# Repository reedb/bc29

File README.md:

Generate a schematic for the Brusa BC29 Ampere hour meter in CADSOFT Eagle format.

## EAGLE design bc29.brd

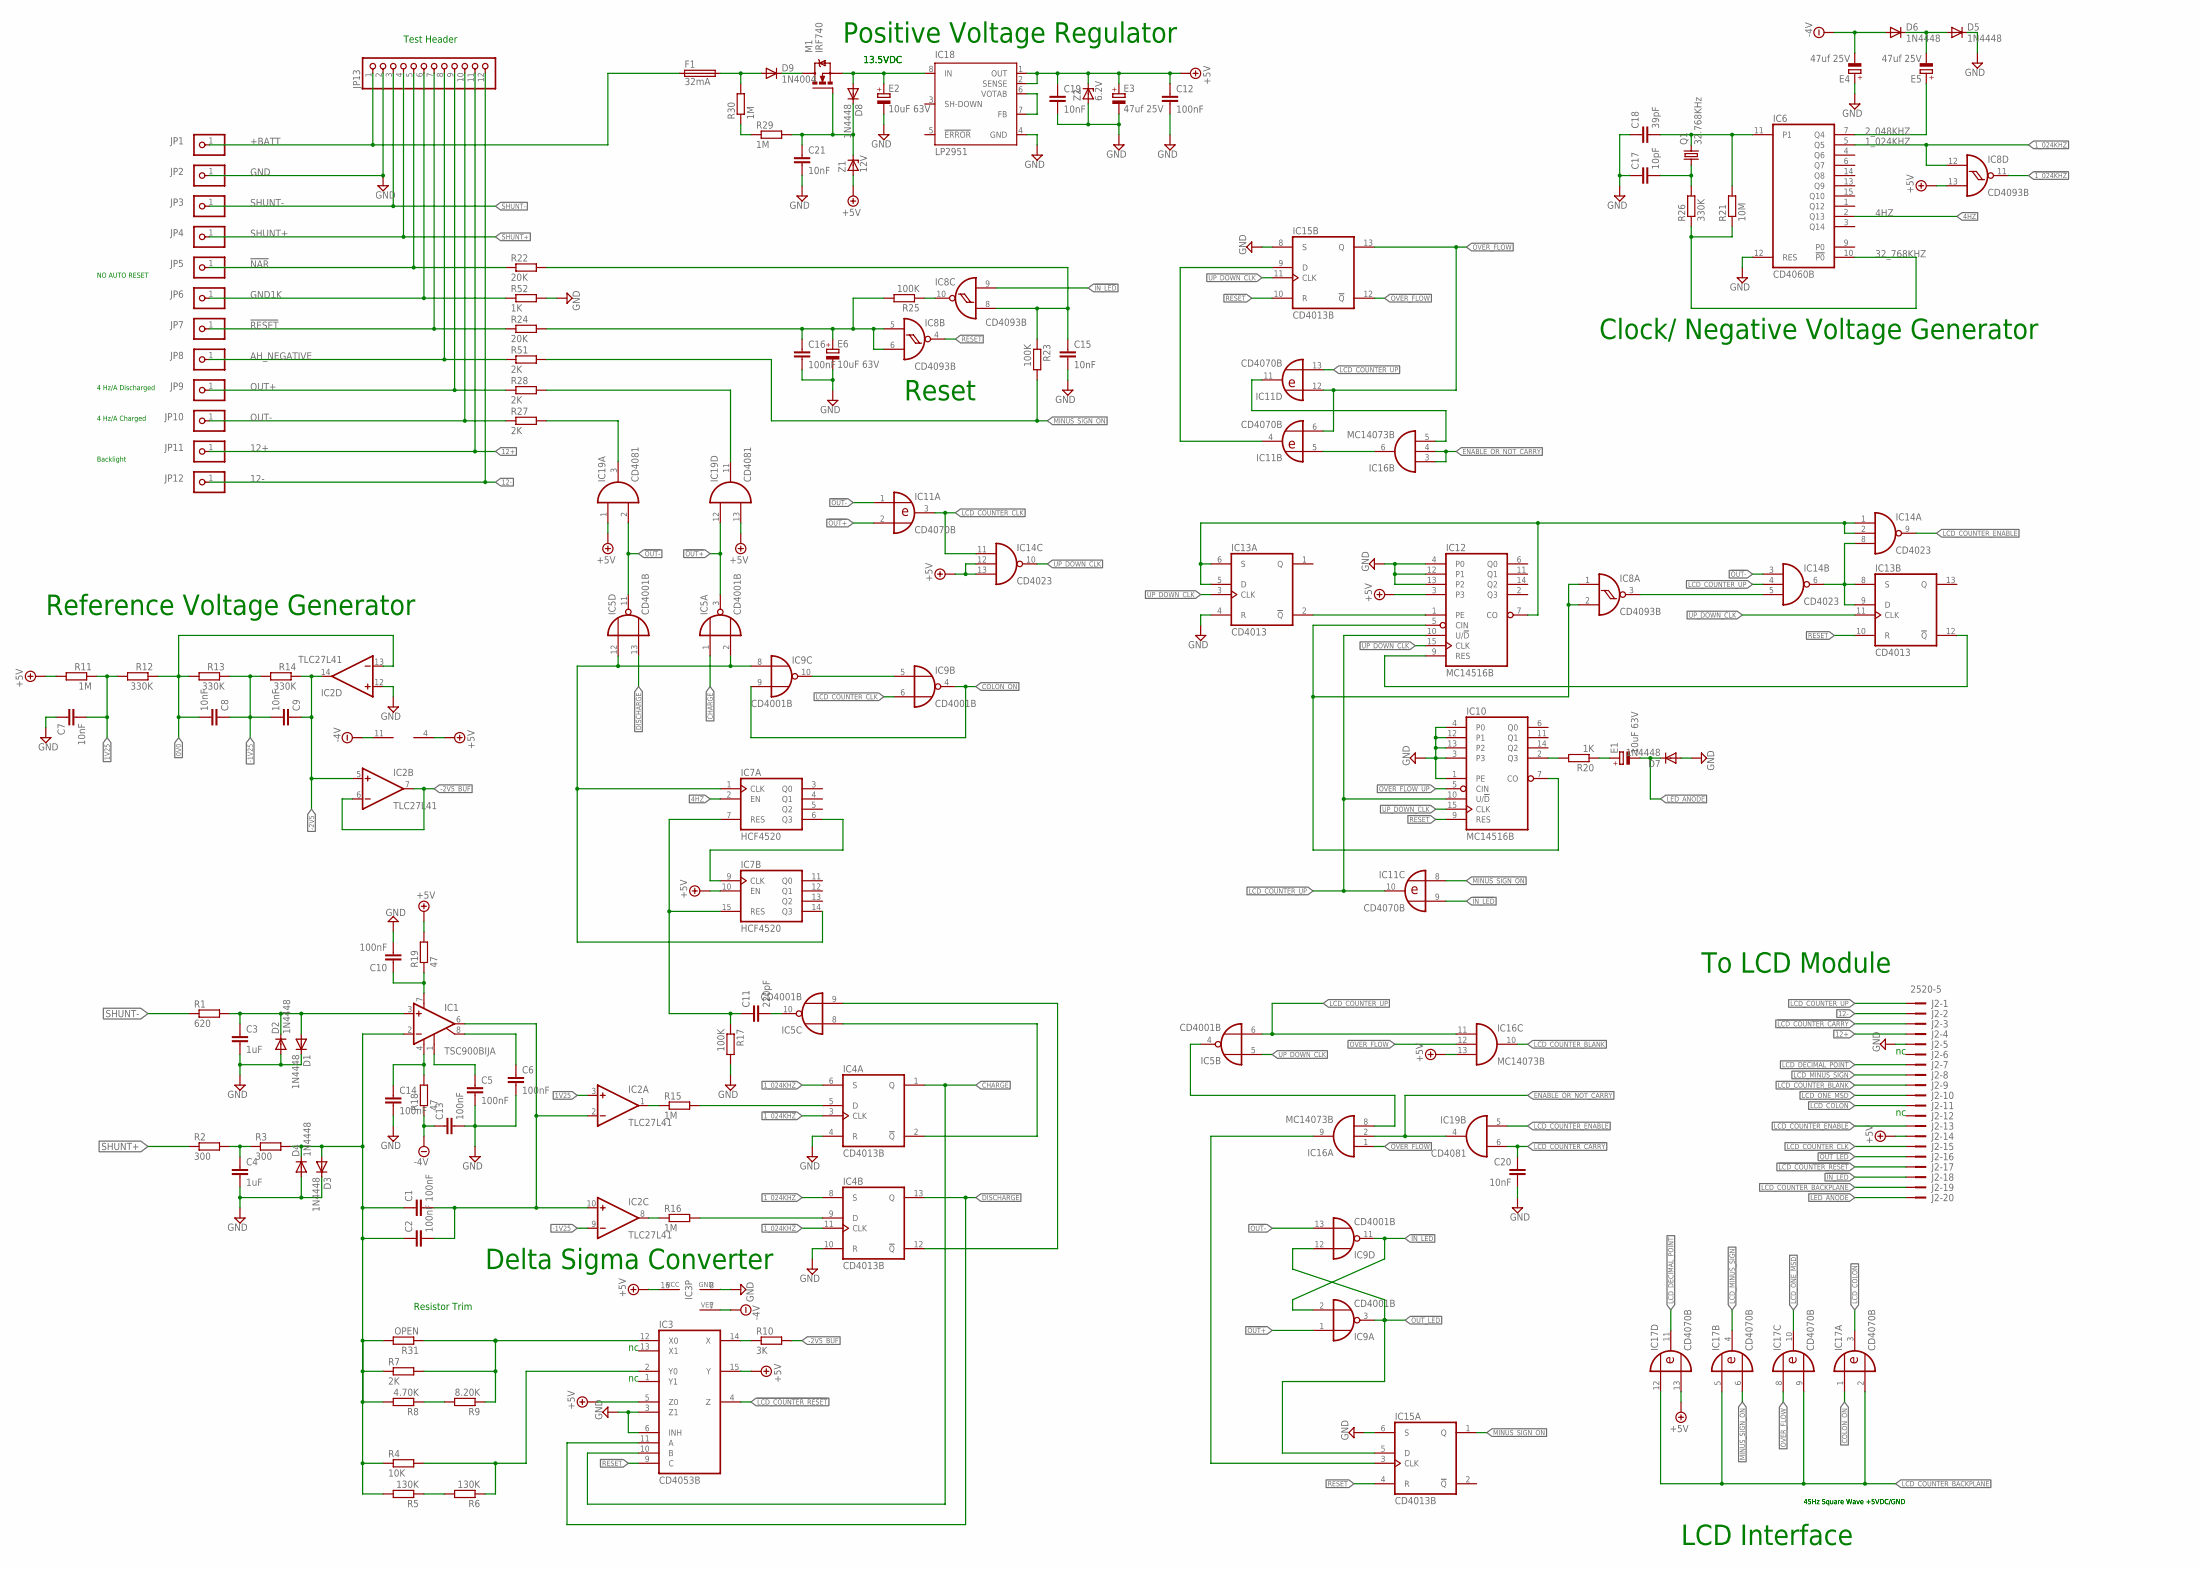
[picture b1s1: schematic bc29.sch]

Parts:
C1, C2, C5, C6, C10, C12, C13, C14, C16: 100nF; C1206
C3, C4: 1uF; C050-045X075
C7, C8, C9, C15, C19, C21: 10nF; C0805
C11: 220pF; C0805
C17: 10pF; C0805
C18: 39pF; C0805
C20: 10nF; C050-024X044
D1, D2, D3, D4, D5, D6, D7, D8: 1N4448; MINIMELF
D9: 1N4004; SOD80C
E1, E2, E6: 10uF 63V; E2,5-5
E3, E4, E5: 47uf 25V; E2,5-5
F1: 32mA; FUSE_HOLDER_5X20MM
IC1: TSC900BIJA; DIL08
IC2: TLC27L41; SO14
IC3: CD4053B; SO16
IC4, IC15: CD4013B; SO14
IC5, IC9: CD4001B; SO14
IC6: CD4060B; SO16
IC7: HCF4520; SO16
IC8: CD4093B; SO14
IC10, IC12: MC14516B; SO16
IC11, IC17: CD4070B; SO14
IC13: CD4013; SO14
IC14: CD4023; SO14
IC16: MC14073B; SO14
IC18: LP2951; SO08
IC19: CD4081; SO14
J2: 2520-5; PAK100/2500-5-20
JP1, JP2, JP3, JP4, JP5, JP6, JP7, JP8, JP9, JP10, JP11, JP12: PINHD-1X1; 1X01
JP13: PINHD-1X12; 1X12
M1: IRF740; TO220BV
Q1: 32.768KHz; TC26H
R1: 620; M0805
R2, R3: 300; M0805
R4: 10K; M0805
R5, R6: 130K; 0207/10
R7, R27, R28, R51: 2K; M0805
R8: 4.70K; 0207/10
R9: 8.20K; 0207/10
R10: 3K; M0805
R11, R15, R16, R29, R30: 1M; M0805
R12, R13, R14, R26: 330K; M0805
R17, R23, R25: 100K; M0805
R18, R19: 47; M0805
R20, R52: 1K; M0805
R21: 10M; M0805
R22, R24: 20K; M0805
R31: OPEN; 0207/10
Z1: 12V; SOD80C
Z2: 6.2V; SOD80C

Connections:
0V0: C8.2, IC2.13 (-IN), R12.1, R13.2
1V25: C7.2, IC2.3 (+IN), R11.1, R12.2
1_024KHZ: IC4.6 (S), IC4.8 (S), IC6.5 (Q5), IC8.12 (I0)
2_048KHZ: E5.+, IC6.7 (Q4)
4HZ: IC6.2 (Q13), IC7.2 (EN)
12+: J2.4, JP11.1, JP13.11
12-: J2.2, JP12.1, JP13.12
13V5: D8.A, E2.+, IC18.8 (IN), M1.S
32_768KHZ: IC6.10 (!P0), R21.1, R26.1
!1_024KHZ: IC4.3 (CLK), IC4.11 (CLK), IC8.11 (O)
!CHARGE: IC4.2 (!Q), IC5.8 (I0)
!DISCHARGE: IC4.12 (!Q), IC5.9 (I1)
!IN_LED: IC8.9 (I1), IC9.2 (I1), IC9.11 (O), IC11.9 (I1), J2.18
!LCD_COUNTER_CARRY: C20.1, IC19.6 (I1), J2.3
!LCD_COUNTER_RESET: IC3.4 (Z), J2.17
!NAR: JP5.1, JP13.5, R22.1
!NAR_R: C15.1, IC8.8 (I0), R22.2, R23.1
!OUT+: IC5.3 (O), IC9.1 (I0), IC11.2 (I1), IC19.12 (I0)
!OUT-: IC5.11 (O), IC9.13 (I1), IC11.1 (I0), IC14.3 (I0), IC19.2 (I1)
!OUT_LED: IC9.3 (O), IC9.12 (I0), IC15.5 (D), J2.16
!OVER_FLOW: IC15.12 (!Q), IC16.1 (I0)
!RESET: JP7.1, JP13.7, R24.1
+5V: C12.1, C19.1, E3.+, IC2.4 (V+), IC3.5 (Z0), IC3.15 (Y), IC3.16 (VCC), IC7.10 (EN), IC8.13 (I1), IC12.3, IC14.12 (I1), IC14.13 (I2), IC16.13 (I2), IC17.13 (I1), IC18.1 (OUT), IC18.2 (SENSE), IC19.1 (I0), IC19.13 (I1), J2.14, R11.2, R19.2, Z1.A, Z2.C
+BATT: F1.1, JP1.1, JP13.1
-1V25: C8.1, C9.2, IC2.9 (-IN), R13.1, R14.2
-2V5: C9.1, IC2.5 (+IN), IC2.14 (OUT), R14.1
-2V5_BUF: IC2.6 (-IN), IC2.7 (OUT), R10.2
-2V5_BUF_R: IC3.14 (X), R10.1
-4V: D6.A, E4.-
-5V: C13.1, IC2.11 (V-), IC3.7 (VEE), R18.1
AH_NEGATIVE: JP8.1, JP13.8, R51.1
CHARGE: IC3.10 (B), IC4.1 (Q), IC5.1 (I0)
COLON_ON: IC9.4 (O), IC9.9 (I1), IC17.1 (I0)
CXA: C5.1, IC1.1 (CMP1)
CXB: C6.1, IC1.8 (CMP2)
DISCHARGE: IC3.11 (A), IC4.13 (Q), IC5.13 (I1)
DRAIN: D9.C, M1.D
D_CHARGE: IC4.5 (D), R15.2
D_DISCHARGE: IC4.9 (D), R16.2
ENABLE_OR_NOT_CARRY: IC16.2 (I1), IC16.3 (I0), IC16.4 (I1), IC19.4 (O)
FUSED_BATT+: D9.A, F1.2, R30.2
GATE: C21.1, D8.C, M1.G, R29.2, Z1.C
GND: C3.2, C4.2, C5.2, C6.2, C7.1, C10.2, C12.2, C13.2, C14.2, C15.2, C16.2, C17.1, C18.1, C19.2, C20.2, C21.2, D1.C, D2.A, D3.C, D4.A, D5.C, D7.A, E2.-, E3.-, E4.+, E6.-, IC2.12 (+IN), IC3.3 (Z1), IC3.6 (INH), IC3.8 (GND), IC4.4 (R), IC4.10 (R), IC6.12 (RES), IC10.1 (PE), IC10.3, IC10.4 (P0), IC10.12 (P1), IC10.13 (P2), IC12.4 (P0), IC12.12 (P1), IC12.13 (P2), IC13.4 (R), IC15.6 (S), IC15.8 (S), IC18.4 (GND), J2.5, JP2.1, JP13.2, R17.2, R52.2, Z2.A
GND1K: JP6.1, JP13.6, R52.1
IC3-11: IC11.11 (O), IC16.5 (I2)
IC5-4: IC5.4 (O), IC16.8 (I2)
IC7-14: IC5.2 (I1), IC5.12 (I0), IC7.1 (CLK), IC7.14 (Q3), IC9.8 (I0)
IC8-3: IC8.3 (O), IC14.5 (I2)
IC10-7: IC8.1 (I0), IC8.2 (I1), IC10.7 (CO), IC12.5 (CIN)
IC13-5: IC12.7 (CO), IC13.5 (D), IC13.6 (S), IC14.1 (I0), IC14.2 (I1)
IC14-6: IC13.8 (S), IC13.9 (D), IC14.6 (O), IC14.8 (I2)
IC15-3: IC15.3 (CLK), IC16.9 (O)
IN+: C3.1, D1.A, D2.C, IC1.3 (+IN), R1.2
IN-: C1.1, C2.1, D3.A, D4.C, IC1.2 (-IN), R3.2, R4.1, R5.2, R7.1, R8.2, R31.2
LCD_COLON: IC17.3 (O), J2.11
LCD_COUNTER_BACKPLANE: IC17.2 (I1), IC17.5 (I0), IC17.9 (I1), IC17.12 (I0), J2.19
LCD_COUNTER_BLANK: IC16.10 (O), J2.9
LCD_COUNTER_CLK: IC9.6 (I1), IC11.3 (O), IC14.11 (I0), J2.15
LCD_COUNTER_ENABLE: IC14.9 (O), IC19.5 (I0), J2.13
LCD_COUNTER_UP: IC5.6 (I1), IC10.10 (U/!D), IC11.10 (O), IC11.13 (I1), IC12.10 (U/!D), IC14.4 (I1), IC16.11 (I0), J2.1
LCD_DECIMAL_POINT: IC17.11 (O), J2.7
LCD_MINUS_SIGN: IC17.4 (O), J2.8
LCD_ONE_MSD: IC17.10 (O), J2.10
LED_ANODE: D7.C, E1.-, J2.20
MINUS_SIGN_ON: IC11.8 (I0), IC15.1 (Q), IC17.6 (I1), R23.2, R51.2
unnamed: C11.2, IC5.10 (O)
unnamed: IC12.9 (RES), IC13.12 (!Q)
unnamed: IC11.4 (O), IC15.9 (D)
unnamed: IC12.1 (PE), IC13.2 (!Q)
unnamed: IC7.6 (Q3), IC7.9 (CLK)
unnamed: C11.1, IC7.7 (RES), IC7.15 (RES), R17.1
unnamed: IC9.5 (I0), IC9.10 (O)
unnamed: IC11.5 (I0), IC16.6 (O)
unnamed: R29.1, R30.1
unnamed: IC10.2 (Q3), R20.2
unnamed: D5.A, D6.C, E5.-
unnamed: C17.2, Q1.1, R26.2
unnamed: C18.2, IC6.11 (P1), Q1.2, R21.2
unnamed: R5.1, R6.2
unnamed: IC18.6 (VOTAB), IC18.7 (FB)
unnamed: R8.1, R9.2
unnamed: IC8.10 (O), R25.1
unnamed: E1.+, R20.1
NEG_COMPARATOR: IC2.8 (OUT), R16.1
OP_AMP__OUT: C1.2, C2.2, IC1.6 (OUT), IC2.2 (-IN), IC2.10 (+IN)
OUT+: JP9.1, JP13.9, R28.1
OUT+_R: IC19.11 (O), R28.2
OUT-: JP10.1, JP13.10, R27.1
OUT-_R: IC19.3 (O), R27.2
OVER_FLOW: IC11.6 (I1), IC11.12 (I0), IC15.13 (Q), IC16.12 (I1), IC17.8 (I0)
OVER_FLOW_UP: IC10.5 (CIN)
POS_COMPARATOR: IC2.1 (OUT), R15.1
RESET: IC3.9 (C), IC8.4 (O), IC10.9 (RES), IC13.10 (R), IC15.4 (R), IC15.10 (R)
RESET_R: C16.1, E6.+, IC8.5 (I0), IC8.6 (I1), R24.2, R25.2
SHUNT+: JP4.1, JP13.4, R2.1
SHUNT+FILTER: C4.1, R2.2, R3.1
SHUNT-: JP3.1, JP13.3, R1.1
UP_DOWN_CLK: IC5.5 (I0), IC10.15 (CLK), IC12.15 (CLK), IC13.3 (CLK), IC13.11 (CLK), IC14.10 (O), IC15.11 (CLK)
VDD: IC4.14 (VDD), IC5.14 (VDD), IC6.16 (VDD), IC7.16 (VDD), IC8.14 (VDD), IC9.14 (VDD), IC10.16 (VDD), IC11.14 (VDD), IC12.16 (VDD), IC13.14 (VDD), IC14.14 (VDD), IC15.14 (VDD), IC16.14 (VDD), IC17.14 (VDD), IC19.14 (VDD)
VDD+: C10.1, IC1.7 (V+), R19.1
VDD-: C14.1, IC1.4 (V-), R18.2
VSS: IC4.7 (VSS), IC5.7 (VSS), IC6.8 (VSS), IC7.8 (VSS), IC8.7 (VSS), IC9.7 (VSS), IC10.8 (VSS), IC11.7 (VSS), IC12.8 (VSS), IC13.7 (VSS), IC14.7 (VSS), IC15.7 (VSS), IC16.7 (VSS), IC17.7 (VSS), IC19.7 (VSS)
X0: IC3.12 (X0), R7.2, R9.1, R31.1
Y0: IC3.2 (Y0), R4.2, R6.1

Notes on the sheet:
Test Header
13.5VDC
Resistor Trim
Delta Sigma Converter
NO AUTO RESET
4 Hz/A Discharged
4 Hz/A Charged
Backlight
Reference Voltage Generator
LCD Interface
Clock/ Negative Voltage Generator
Positive Voltage Regulator
To LCD Module
45Hz Square Wave +5VDC/GND
Reset

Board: 2 copper layers, 107 parts (0 on the bottom side), 103 nets, no tracks yet.

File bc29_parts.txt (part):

Partlist

Exported from bc29.sch at 2014-12-11 8:26 AM

EAGLE Version 7.1.0 Copyright (c) 1988-2014 CadSoft

Assembly variant: 

Part     Value          Device            Package            Library          Sheet

C1       100nF          C-EUC1206         C1206              rcl              1
C2       100nF          C-EUC1206         C1206              rcl              1
C3       1uF            C-EU050-045X075   C050-045X075       rcl              1
C4       1uF            C-EU050-045X075   C050-045X075       rcl              1
C5       100nF          C-EUC1206         C1206              rcl              1
C6       100nF          C-EUC1206         C1206              rcl              1
C7       10nF           C-EUC0805         C0805              rcl              1
C8       10nF           C-EUC0805         C0805              rcl              1
C9       10nF           C-EUC0805         C0805              rcl              1
C10      100nF          C-EUC1206         C1206              rcl              1
C11      220pF          C-EUC0805         C0805              rcl              1
C12      100nF          C-EUC1206         C1206              rcl              1
C13      100nF          C-EUC1206         C1206              rcl              1
C14      100nF          C-EUC1206         C1206              rcl              1
C15      10nF           C-EUC0805         C0805              rcl              1
C16      100nF          C-EUC1206         C1206              rcl              1
C17      10pF           C-EUC0805         C0805              rcl              1
C18      39pF           C-EUC0805         C0805              rcl              1
C19      10nF           C-EUC0805         C0805              rcl              1
C20      10nF           C-EU050-024X044   C050-024X044       rcl              1
C21      10nF           C-EUC0805         C0805              rcl              1
D1       1N4448         DIODE-MINIMELF    MINIMELF           diode            1
D2       1N4448         DIODE-MINIMELF    MINIMELF           diode            1
D3       1N4448         DIODE-MINIMELF    MINIMELF           diode            1
D4       1N4448         DIODE-MINIMELF    MINIMELF           diode            1
D5       1N4448         DIODE-MINIMELF    MINIMELF           diode            1
D6       1N4448         DIODE-MINIMELF    MINIMELF           diode            1
D7       1N4448         DIODE-MINIMELF    MINIMELF           diode            1
D8       1N4448         DIODE-MINIMELF    MINIMELF           diode            1
D9       1N4004         DIODE-SOD80C      SOD80C             diode            1
E1       10uF 63V       CPOL-EUE2.5-5     E2,5-5             rcl              1
E2       10uF 63V       CPOL-EUE2.5-5     E2,5-5             rcl              1
E3       47uf 25V       CPOL-EUE2.5-5     E2,5-5             rcl              1
E4       47uf 25V       CPOL-EUE2.5-5     E2,5-5             rcl              1
E5       47uf 25V       CPOL-EUE2.5-5     E2,5-5             rcl              1
E6       10uF 63V       CPOL-EUE2.5-5     E2,5-5             rcl              1
F1       32mA           FUSEBLANK_5X20MM  FUSE_HOLDER_5X20MM fuse             1
IC1      TSC900BIJA     2CMPN             DIL08              linear           1
IC2      TLC27L41       TLC274D           SO14               linear           1
IC3      CD4053B        4053D             SO16               40xx             1
IC4      CD4013B        4013D             SO14               40xx             1
IC5      CD4001B        4001D             SO14               40xx             1
IC6      CD4060B        4060D             SO16               40xx             1
IC7      HCF4520        4520D             SO16               45xx             1
IC8      CD4093B        4093D             SO14               40xx             1
IC9      CD4001B        4001D             SO14               40xx             1
IC10     MC14516B       4516D             SO16               45xx             1
IC11     CD4070B        4070D             SO14               40xx             1
IC12     MC14516B       4516D             SO16               45xx             1
IC13     CD4013         4013D             SO14               40xx             1
IC14     CD4023         4023D             SO14               40xx             1
IC15     CD4013B        4013D             SO14               40xx             1
IC16     MC14073B       4073D             SO14               40xx             1
IC17     CD4070B        4070D             SO14               40xx             1
IC18     LP2951         LP2951D           SO08               linear           1
IC19     CD4081         4081D             SO14               40xx             1
J1       2520-5         2520-5            PAK100/2500-5-20   con-3m           1
JP1                     PINHD-1X1         1X01               pinhead          1
JP2                     PINHD-1X1         1X01               pinhead          1
JP3                     PINHD-1X1         1X01               pinhead          1
JP4                     PINHD-1X1         1X01               pinhead          1
JP5                     PINHD-1X1         1X01               pinhead          1
JP6                     PINHD-1X1         1X01               pinhead          1
JP7                     PINHD-1X1         1X01               pinhead          1
JP8                     PINHD-1X1         1X01               pinhead          1
JP9                     PINHD-1X1         1X01               pinhead          1
JP10                    PINHD-1X1         1X01               pinhead          1
JP11                    PINHD-1X1         1X01               pinhead          1
JP12                    PINHD-1X1         1X01               pinhead          1
JP13                    PINHD-1X12        1X12               pinhead          1
M1       IRF740         IRF740            TO220BV            transistor-power 1
Q1       32.768KHz      CRYSTALTC26H      TC26H              crystal          1
R1       620            R-EU_M0805        M0805              rcl              1
R2       300            R-EU_M0805        M0805              rcl              1
R3       300            R-EU_M0805        M0805              rcl              1
R4       10K            R-EU_M0805        M0805              rcl              1
R5       130K           R-EU_0207/10      0207/10            rcl              1
R6       130K           R-EU_0207/10      0207/10            rcl              1
R7       2K             R-EU_M0805        M0805              rcl              1
R8       4.70K          R-EU_0207/10      0207/10            rcl              1
R9       8.20K          R-EU_0207/10      0207/10            rcl              1
R10      3K             R-EU_M0805        M0805              rcl              1
R11      1M             R-EU_M0805        M0805              rcl              1
R12      330K           R-EU_M0805        M0805              rcl              1
R13      330K           R-EU_M0805        M0805              rcl              1
R14      330K           R-EU_M0805        M0805              rcl              1
R15      1M             R-EU_M0805        M0805              rcl              1
R16      1M             R-EU_M0805        M0805              rcl              1
R17      100K           R-EU_M0805        M0805              rcl              1
R18      47             R-EU_M0805        M0805              rcl              1
R19      47             R-EU_M0805        M0805              rcl              1
R20      1K             R-EU_M0805        M0805              rcl              1
R21      10M            R-EU_M0805        M0805              rcl              1
R22      20K            R-EU_M0805        M0805              rcl              1
R23      100K           R-EU_M0805        M0805              rcl              1
R24      20K            R-EU_M0805        M0805              rcl              1
R25      100K           R-EU_M0805        M0805              rcl              1
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
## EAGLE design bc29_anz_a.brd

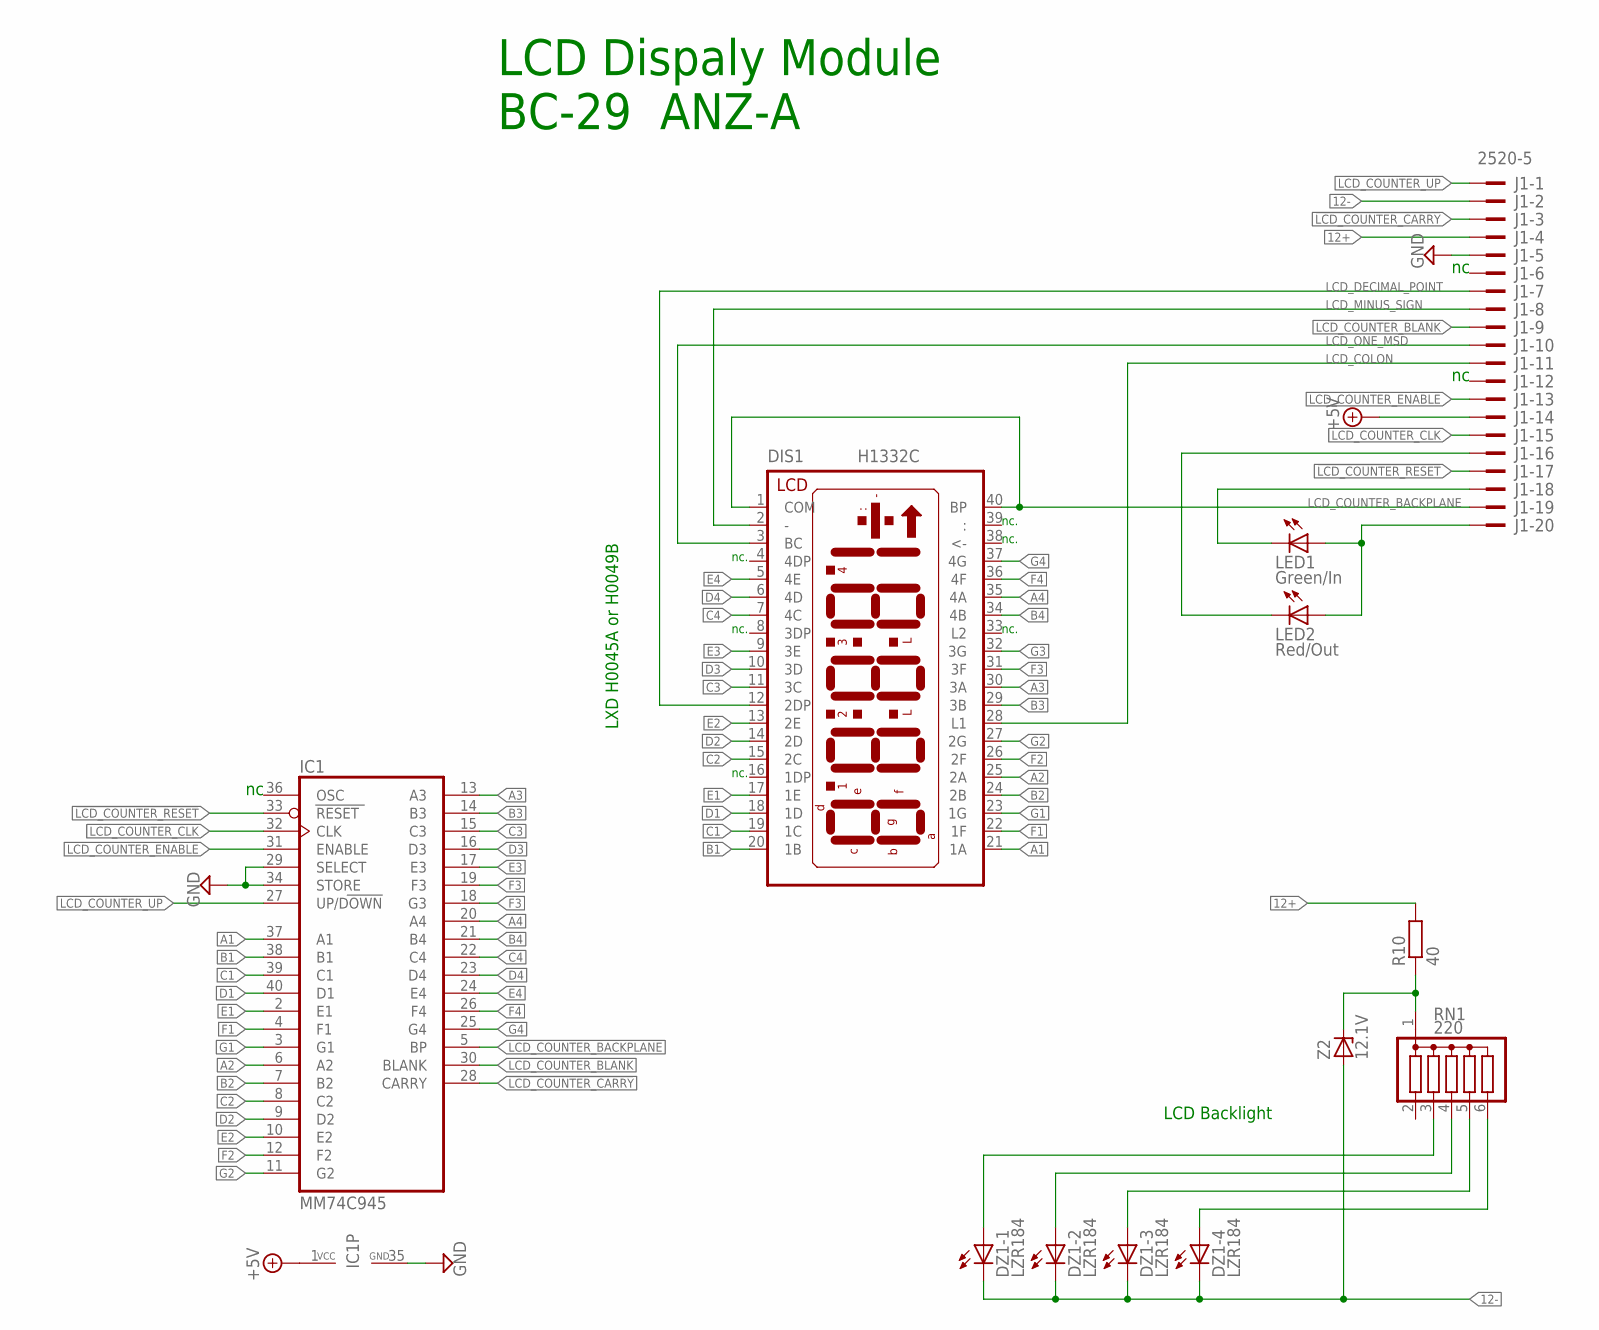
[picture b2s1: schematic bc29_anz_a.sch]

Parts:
DIS1: H1332C
DZ1: LZR184
IC1: MM74C945; DIL40
J1: 2520-5; PAK100/2500-5-20
LED1: Green/In; LED5MM
LED2: Red/Out; LED5MM
R10: 40; 0207/10
RN1: 220; SIL6
Z2: 12.1V; SOD80C

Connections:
12+: J1.4, R10.2
12-: DZ1.K1 (C), DZ1.K2 (C), DZ1.K3 (C), DZ1.K4 (C), J1.2, Z2.A
!IN_LED: J1.18, LED1.K (C)
!LCD_COUNTER_CARRY: IC1.28 (CARRY), J1.3
!LCD_COUNTER_RESET: IC1.33 (RESET), J1.17
!OUT_LED: J1.16, LED2.K (C)
+5V: J1.14
+12V: IC1.1 (VCC)
A1: DIS1.21 (1A), IC1.37 (A1)
A2: DIS1.25 (2A), IC1.6 (A2)
A3: DIS1.30 (3A), IC1.13 (A3)
A4: DIS1.35 (4A), IC1.20 (A4)
B1: DIS1.20 (1B), IC1.38 (B1)
B2: DIS1.24 (2B), IC1.7 (B2)
B3: DIS1.29 (3B), IC1.14 (B3)
B4: DIS1.34 (4B), IC1.21 (B4)
BL0: DZ1.A1 (A), RN1.3
BL1: DZ1.A2 (A), RN1.4
BL2: DZ1.A3 (A), RN1.5
BL3: DZ1.A4 (A), RN1.6
C1: DIS1.19 (1C), IC1.39 (C1)
C2: DIS1.15 (2C), IC1.8 (C2)
C3: DIS1.11 (3C), IC1.15 (C3)
C4: DIS1.7 (4C), IC1.22 (C4)
D1: DIS1.18 (1D), IC1.40 (D1)
D2: DIS1.14 (2D), IC1.9 (D2)
D3: DIS1.10 (3D), IC1.16 (D3)
D4: DIS1.6 (4D), IC1.23 (D4)
E1: DIS1.17 (1E), IC1.2 (E1)
E2: DIS1.13 (2E), IC1.10 (E2)
E3: DIS1.9 (3E), IC1.17 (E3)
E4: DIS1.5 (4E), IC1.24 (E4)
F1: DIS1.22 (1F), IC1.4 (F1)
F2: DIS1.26 (2F), IC1.12 (F2)
F3: DIS1.31 (3F), IC1.19 (F3)
F4: DIS1.36 (4F), IC1.26 (F4)
G1: DIS1.23 (1G), IC1.3 (G1)
G2: DIS1.27 (2G), IC1.11 (G2)
G3: DIS1.32 (3G), IC1.18 (G3)
G4: DIS1.37 (4G), IC1.25 (G4)
GND: IC1.29 (SELECT), IC1.34 (STORE), IC1.35 (GND), J1.5
LCD_COLON: DIS1.28 (L1), J1.11
LCD_COUNTER_BACKPLANE: DIS1.1 (COM), DIS1.40 (BP), IC1.5 (BP), J1.19
LCD_COUNTER_BLANK: IC1.30 (BLANK), J1.9
LCD_COUNTER_CLK: IC1.32 (CLK), J1.15
LCD_COUNTER_ENABLE: IC1.31 (ENABLE), J1.13
LCD_COUNTER_UP: IC1.27 (UP/DOWN), J1.1
LCD_DECIMAL_POINT: DIS1.12 (2DP), J1.7
LCD_MINUS_SIGN: DIS1.2 (-), J1.8
LCD_ONE_MSD: DIS1.3 (BC), J1.10
LED_ANODE: J1.20, LED1.A, LED2.A
LED_V+: R10.1, RN1.1, Z2.C

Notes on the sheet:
LCD Dispaly Module
BC-29 ANZ-A
LXD H0045A or H0049B
LCD Backlight
nc.

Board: 2 copper layers, 9 parts (0 on the bottom side), 50 nets, no tracks yet.

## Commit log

2014-11-15 add readme
2014-11-15 Add troubleshooting files
2014-11-29 Crop and find rotate image
2014-11-29 fix bad pdf
2014-11-29 Repacement for chopper stabilized op amp
2014-12-02 Complete board silk screen. Update schematic to match
2014-12-02 Add multiplexer data sheet
2014-12-02 Charge/discharge output
2014-12-03 more charge/discharge
2014-12-04 Digital updates
2014-12-05 cleanup up/down counter
2014-12-06 cleanup random gates
2014-12-08 Change reference designators and capacitor values to match 'Official' schematic
2014-12-12 add data sheets
2014-12-12 add last capacitor values
2014-12-12 update lcd interface portion
2014-12-19 Add mm74c945n datasheet. Used in display module
2014-12-19 Add display module
2014-12-19 Incorperate display module knowldge
2014-12-20 Move things around. Update png files
2014-12-25 Clean up net names
2014-12-27 Clean up some net names
2015-01-09 Rference files on Yahoo Solectria_EV site
